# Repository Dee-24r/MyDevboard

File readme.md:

# D-BOARD 2026
This is my devboard! Built on the RP2040 chip, i wired flash storage, a crystal oscillator, usb-c receptacle, and broke out header pins for it. I love it so muchh!

It's purple when produced. look through all the images and journal.md!

## Images

### Schematic

### PCB Layout

### 3D Front View

### 3D Back View

### 3D Cool View

[<video controls src="images/dboard.mp4" title="Title"></video>](https://github.com/user-attachments/assets/dc549047-71fd-4562-b874-6a0587e34dc4)

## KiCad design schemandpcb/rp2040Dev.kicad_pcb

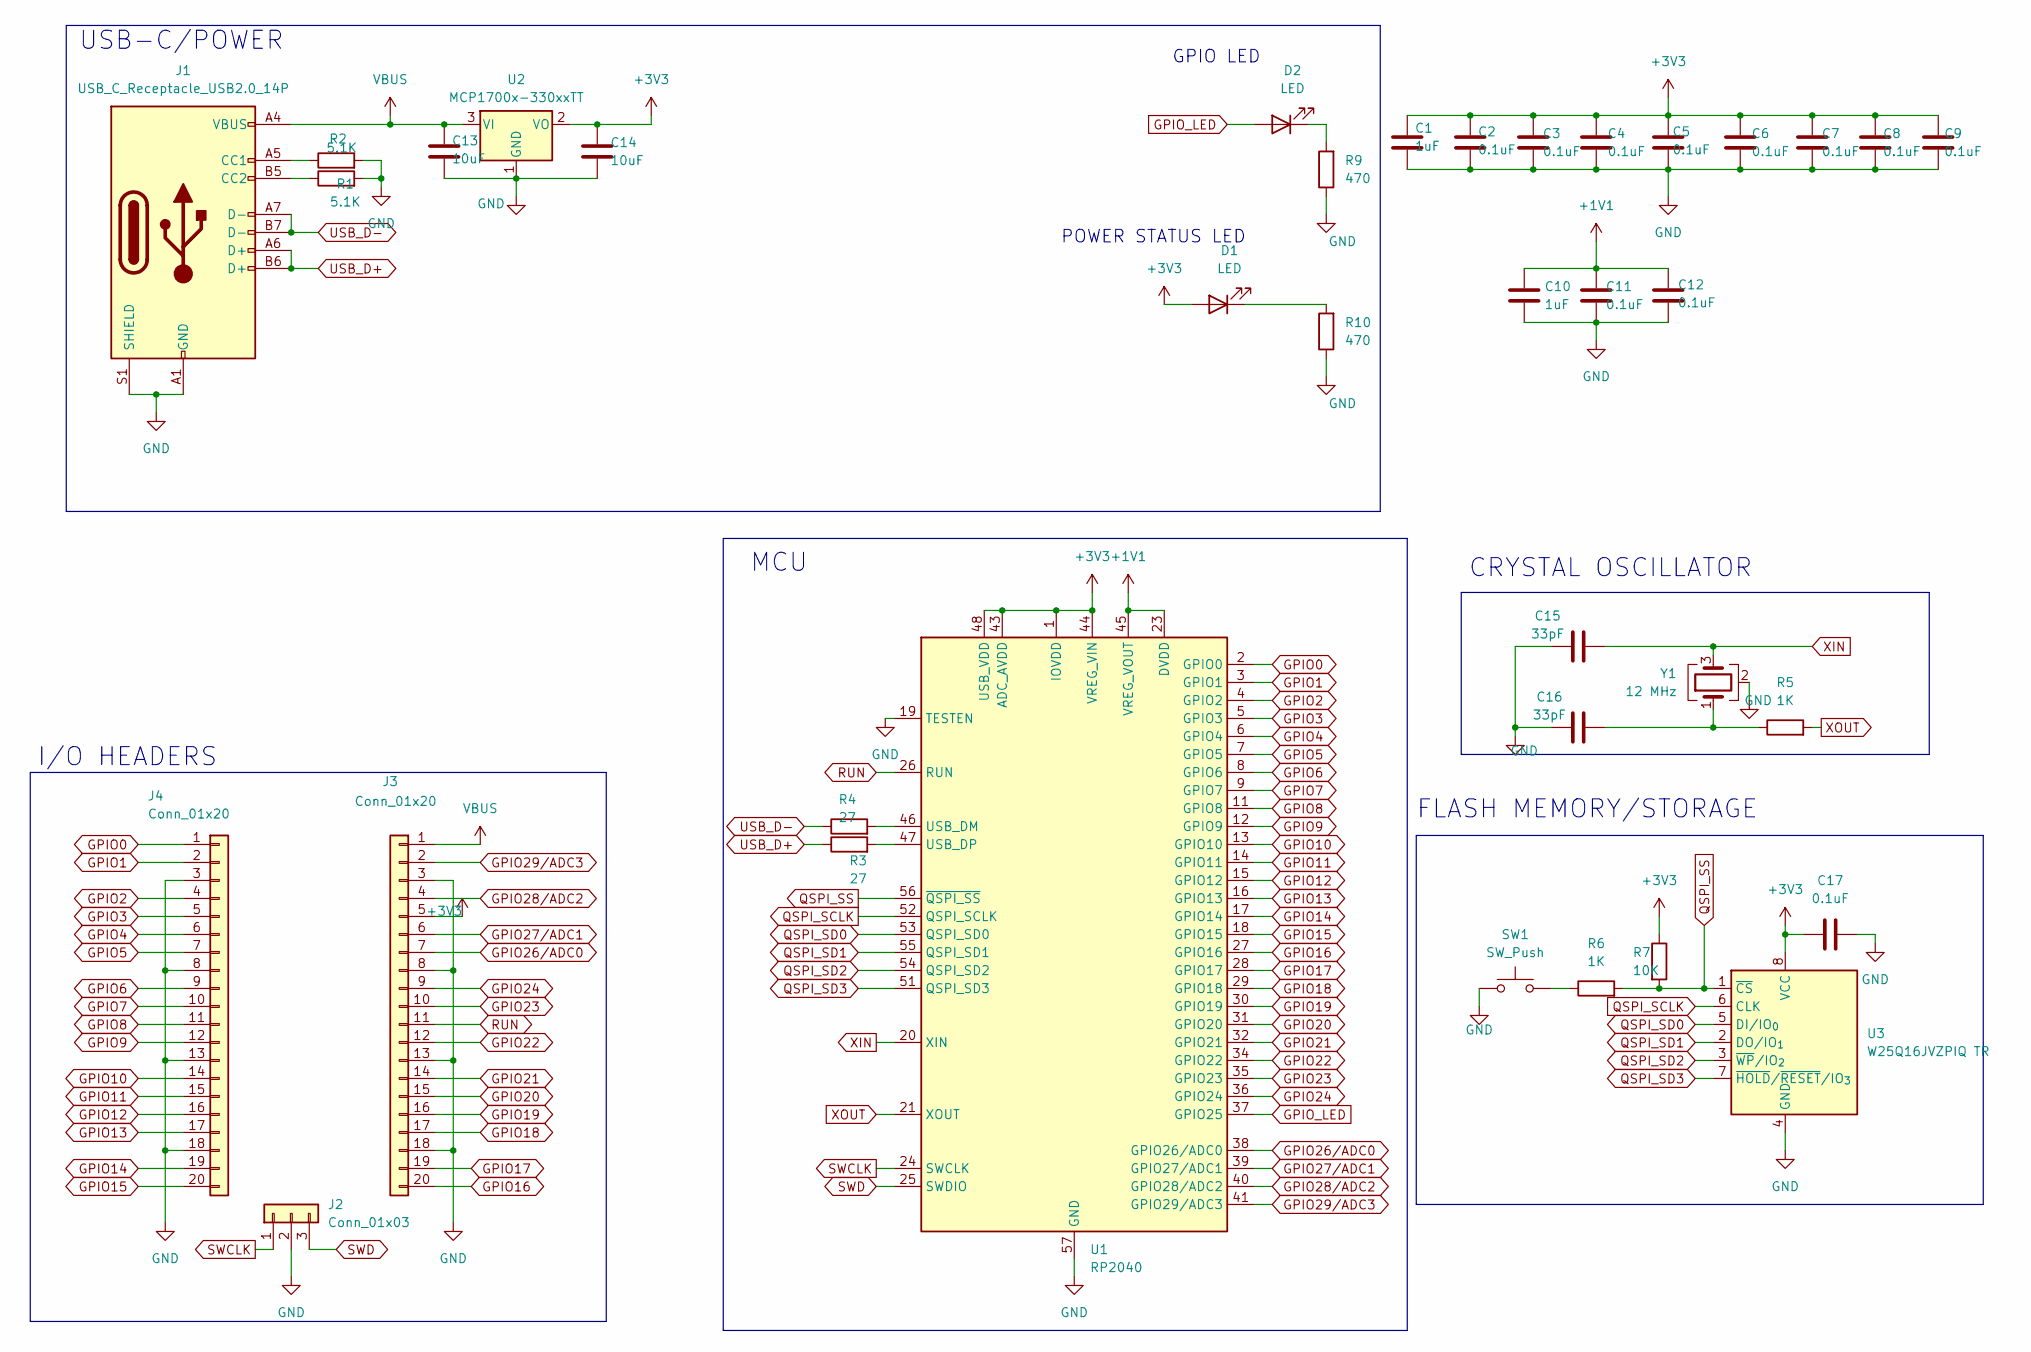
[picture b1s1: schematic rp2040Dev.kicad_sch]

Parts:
C1, C10: 1uF; C_0402_1005Metric
C2, C3, C4, C5, C6, C7, C8, C9, C11, C12, C17: 0.1uF; C_0402_1005Metric
C13, C14: 10uF; C_0603_1608Metric
C15, C16: 33pF; C_0402_1005Metric
D1, D2: LED; LED_0603_1608Metric
J1: USB_C_Receptacle_USB2.0_14P; USB_C_Receptacle_HRO_TYPE-C-31-M-12
J2: Conn_01x03; PinHeader_1x03_P2.54mm_Vertical
J3, J4: Conn_01x20; PinHeader_1x20_P2.54mm_Vertical
R1, R2: 5.1K; R_0402_1005Metric
R3, R4: 27; R_0402_1005Metric
R5, R6: 1K; R_0402_1005Metric
R7: 10K; R_0402_1005Metric
R9, R10: 470; R_0402_1005Metric
SW1: SW_Push; SW_Push_SPST_NO_Alps_SKRK
U1: RP2040; QFN-56-1EP_7x7mm_P0.4mm_EP3.2x3.2mm
U2: MCP1700x-330xxTT; SOT-23
U3: W25Q16JVZPIQ TR; Winbond_USON-8-1EP_3x2mm_P0.5mm_EP0.2x1.6mm
Y1: 12 MHz; Crystal_SMD_3225-4Pin_3.2x2.5mm

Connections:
+1V1: C10.1, C11.1, C12.1, U1.23 (DVDD), U1.45 (VREG_VOUT), U1.50 (DVDD)
+3V3: C1.1, C2.1, C3.1, C4.1, C5.1, C6.1, C7.1, C8.1, C9.1, C14.1, C17.1, D1.2 (A), J3.5, R7.1, U1.1 (IOVDD), U1.10 (IOVDD), U1.22 (IOVDD), U1.33 (IOVDD), U1.42 (IOVDD), U1.43 (ADC_AVDD), U1.44 (VREG_VIN), U1.48 (USB_VDD), U1.49 (IOVDD), U2.2 (VO), U3.8 (VCC)
GND: C1.2, C2.2, C3.2, C4.2, C5.2, C6.2, C7.2, C8.2, C9.2, C10.2, C11.2, C12.2, C13.2, C14.2, C15.1, C16.1, C17.2, J1.A1 (GND), J1.A12 (GND), J1.B1 (GND), J1.B12 (GND), J1.S1 (SHIELD), J2.2, J3.3, J3.8, J3.13, J3.18, J4.3, J4.8, J4.13, J4.18, R1.2, R2.2, R9.1, R10.1, SW1.1, U1.19 (TESTEN), U1.57 (GND), U2.1 (GND), U3.4 (GND), Y1.2 (G), Y1.4 (G)
GPIO0: J4.1, U1.2 (GPIO0)
GPIO1: J4.2, U1.3 (GPIO1)
GPIO2: J4.4, U1.4 (GPIO2)
GPIO3: J4.5, U1.5 (GPIO3)
GPIO4: J4.6, U1.6 (GPIO4)
GPIO5: J4.7, U1.7 (GPIO5)
GPIO6: J4.9, U1.8 (GPIO6)
GPIO7: J4.10, U1.9 (GPIO7)
GPIO8: J4.11, U1.11 (GPIO8)
GPIO9: J4.12, U1.12 (GPIO9)
GPIO10: J4.14, U1.13 (GPIO10)
GPIO11: J4.15, U1.14 (GPIO11)
GPIO12: J4.16, U1.15 (GPIO12)
GPIO13: J4.17, U1.16 (GPIO13)
GPIO14: J4.19, U1.17 (GPIO14)
GPIO15: J4.20, U1.18 (GPIO15)
GPIO16: J3.20, U1.27 (GPIO16)
GPIO17: J3.19, U1.28 (GPIO17)
GPIO18: J3.17, U1.29 (GPIO18)
GPIO19: J3.16, U1.30 (GPIO19)
GPIO20: J3.15, U1.31 (GPIO20)
GPIO21: J3.14, U1.32 (GPIO21)
GPIO22: J3.12, U1.34 (GPIO22)
GPIO23: J3.10, U1.35 (GPIO23)
GPIO24: J3.9, U1.36 (GPIO24)
GPIO26/ADC0: J3.7, U1.38 (GPIO26/ADC0)
GPIO27/ADC1: J3.6, U1.39 (GPIO27/ADC1)
GPIO28/ADC2: J3.4, U1.40 (GPIO28/ADC2)
GPIO29/ADC3: J3.2, U1.41 (GPIO29/ADC3)
GPIO_LED: D2.2 (A), U1.37 (GPIO25)
unnamed: C16.2, R5.1, Y1.1
unnamed: D1.1 (K), R10.2
unnamed: D2.1 (K), R9.2
unnamed: J1.A5 (CC1), R2.1
unnamed: J1.B5 (CC2), R1.1
unnamed: R6.1, SW1.2
unnamed: R4.2, U1.46 (USB_DM)
unnamed: R3.2, U1.47 (USB_DP)
QSPI_SCLK: U1.52 (QSPI_SCLK), U3.6 (CLK)
QSPI_SD0: U1.53 (QSPI_SD0), U3.5 (DI/IO_{0})
QSPI_SD1: U1.55 (QSPI_SD1), U3.2 (DO/IO_{1})
QSPI_SD2: U1.54 (QSPI_SD2), U3.3 (~WP/IO_{2})
QSPI_SD3: U1.51 (QSPI_SD3), U3.7 (~HOLD/~RESET/IO_{3})
QSPI_SS: R6.2, R7.2, U1.56 (~QSPI_SS), U3.1 (~CS)
RUN: J3.11, U1.26 (RUN)
SWCLK: J2.1, U1.24 (SWCLK)
SWD: J2.3, U1.25 (SWDIO)
USB_D+: J1.A6 (D+), J1.B6 (D+), R3.1
USB_D-: J1.A7 (D-), J1.B7 (D-), R4.1
VBUS: C13.1, J1.A4 (VBUS), J1.A9 (VBUS), J1.B4 (VBUS), J1.B9 (VBUS), J3.1, U2.3 (VI)
XIN: C15.2, U1.20 (XIN), Y1.3
XOUT: R5.2, U1.21 (XOUT)

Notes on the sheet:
USB-C/POWER
GPIO LED
I/O HEADERS
MCU
FLASH MEMORY/STORAGE
POWER STATUS LED
CRYSTAL OSCILLATOR

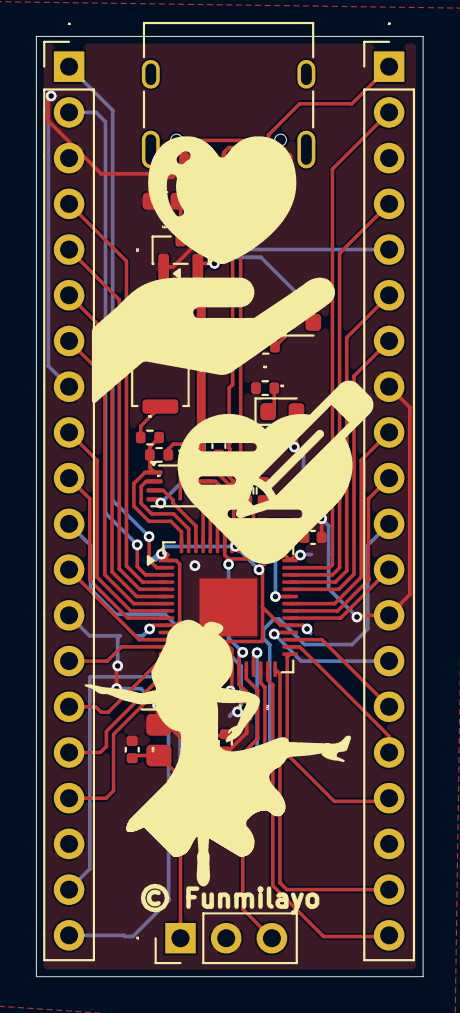
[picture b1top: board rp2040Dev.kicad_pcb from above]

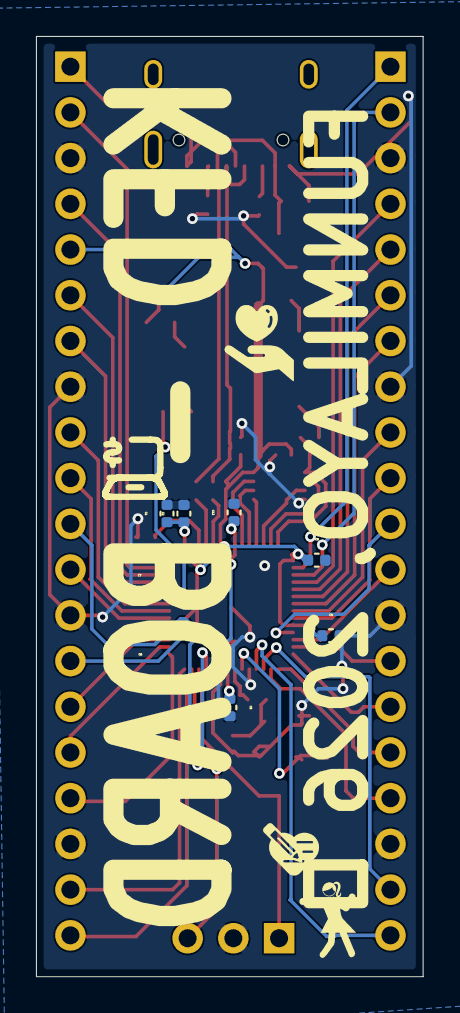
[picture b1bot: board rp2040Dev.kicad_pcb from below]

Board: 2 copper layers, 21.5 x 52.2 mm, 36 parts (8 on the bottom side), 55 nets.

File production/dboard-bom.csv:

Designator,Footprint,Quantity,Value,LCSC Part #
"C1, C10",0402,2,1uF,
"C11, C12, C17, C2, C4, C5, C6, C7, C8, C9",0402,10,0.1uF,
"C13, C14",0603,2,10uF,
"C15, C16",0402,2,33pF,
"D1, D2",0603,2,LED,
J1,USB_C_Receptacle_HRO_TYPE-C-31-M-12,1,USB_C_Receptacle_USB2.0_14P,
J2,PinHeader_1x03_P2.54mm_Vertical,1,Conn_01x03,
"J3, J4",PinHeader_1x20_P2.54mm_Vertical,2,Conn_01x20,
"R1, R2",0402,2,5.1K,
"R10, R9",0402,2,470,
"R3, R4",0402,2,27,
"R5, R6",0402,2,1K,
R7,0402,1,10K,
SW1,SW_Push_SPST_NO_Alps_SKRK,1,SW_Push,
U1,QFN-56-1EP_7x7mm_P0.4mm_EP3.2x3.2mm,1,RP2040,
U2,SOT-23,1,MCP1700x-330xxTT,
U3,Winbond_USON-8-1EP_3x2mm_P0.5mm_EP0.2x1.6mm,1,W25Q16JVZPIQ TR,
Y1,Crystal_SMD_3225-4Pin_3.2x2.5mm,1,12 MHz,

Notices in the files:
schemandpcb/rp2040Dev.kicad_pcb:
© Funmilayo
